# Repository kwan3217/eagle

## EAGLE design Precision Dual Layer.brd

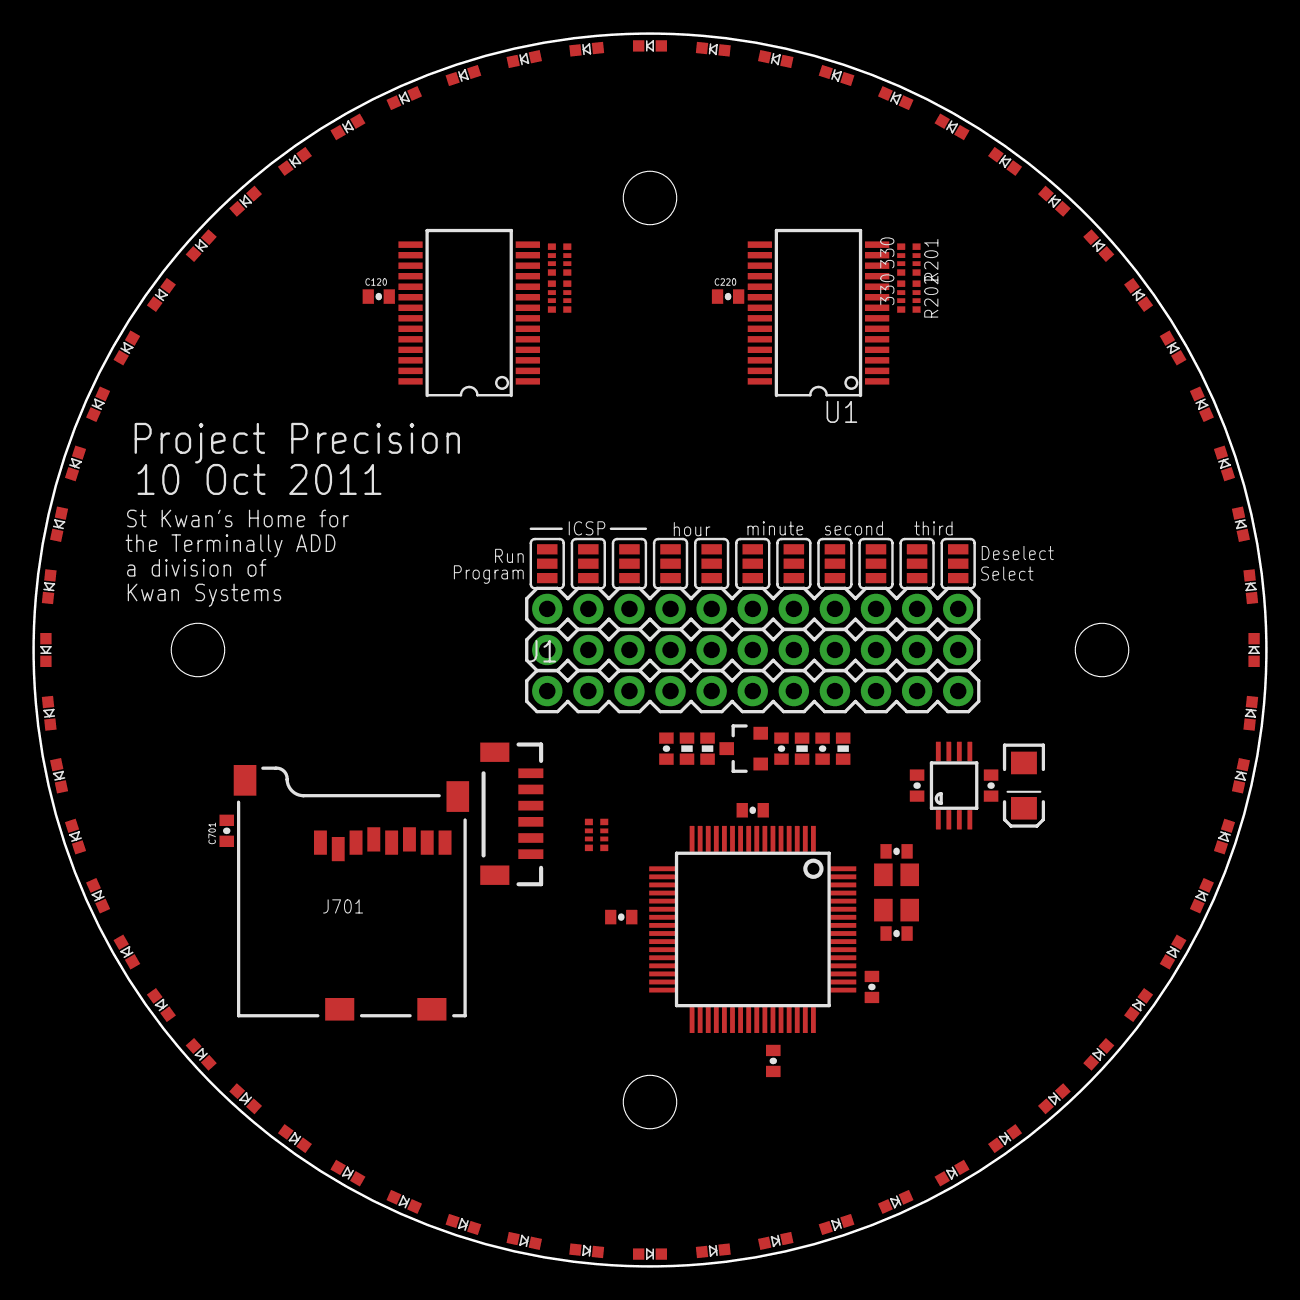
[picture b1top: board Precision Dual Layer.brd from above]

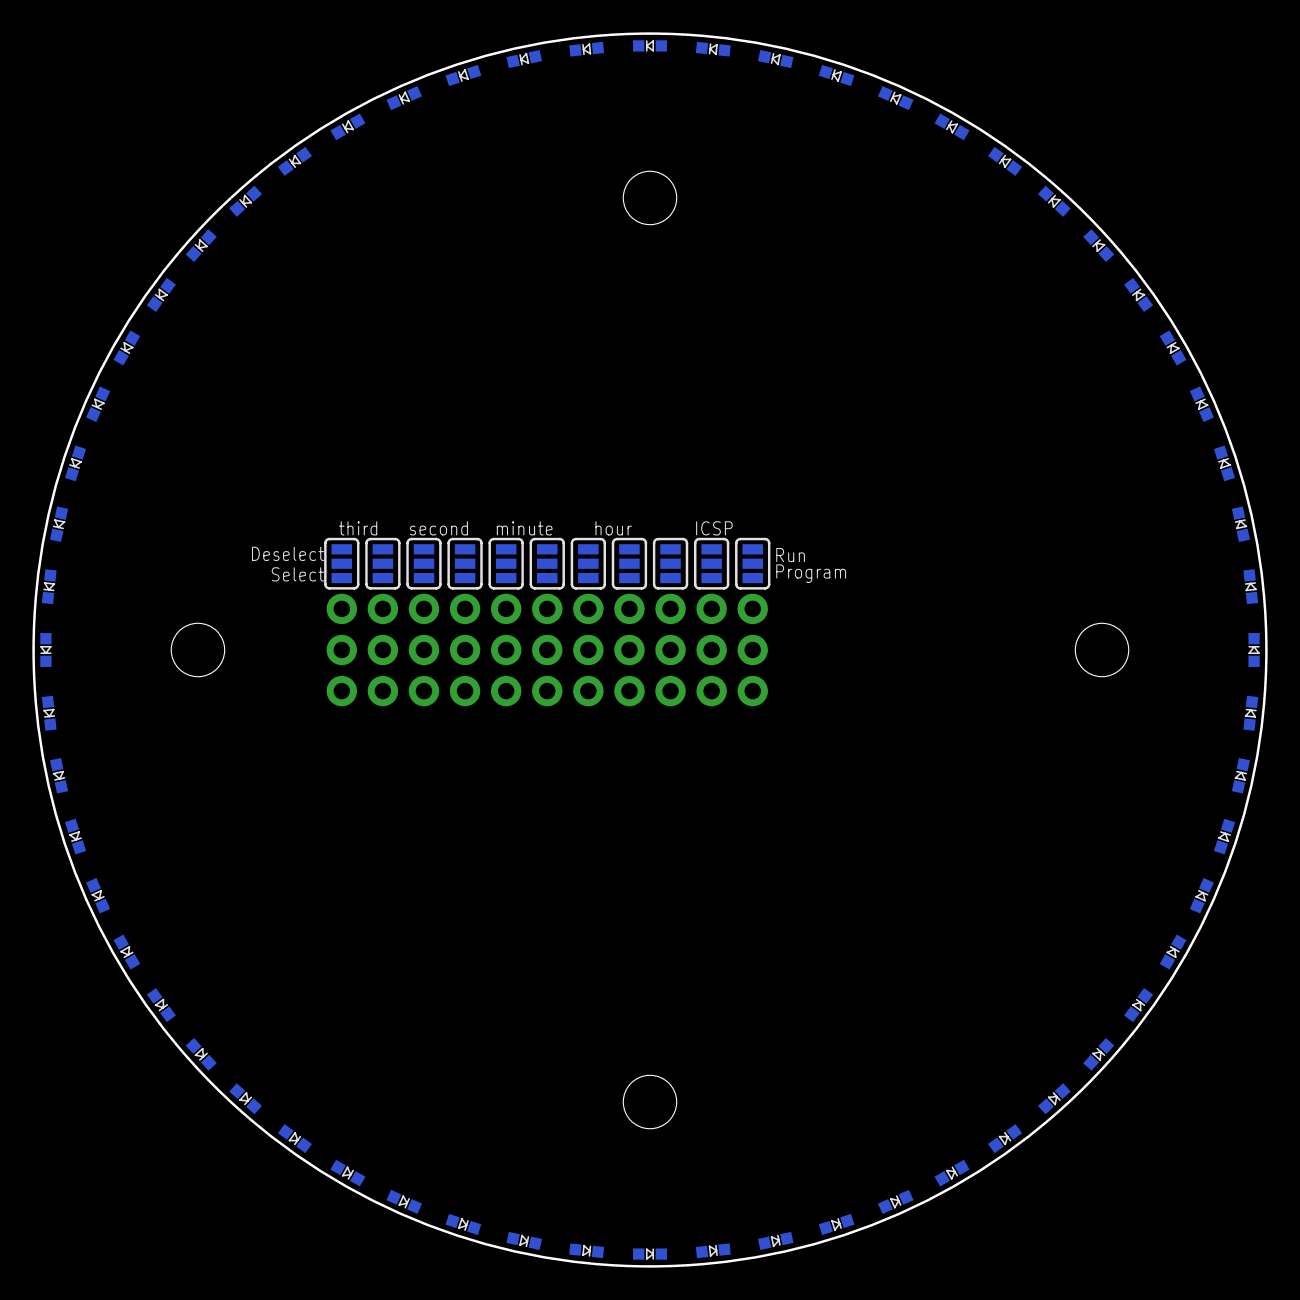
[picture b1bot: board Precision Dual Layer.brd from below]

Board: 2 copper layers, 76.2 x 76.2 mm, 181 parts (71 on the bottom side), 89 nets, no tracks yet.

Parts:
C010, C201: 1uF; 0402-CAP
C020, C030, C461, C462: 18pF; 0402-CAP
C120, C220, C407, C423, C443, C451, C701: 100nF; 0402-CAP
C202: 2.2uF tant; EIA3216
C203: 470pF; 0402-CAP
D00, D01, D02, D03, D04, D05, D06, D07, D08, D09, D10, D11, D12, D13, D14, D15, D16, D17, D18, D19, D20, D21, D22, D23, D24, D25, D26, D27, D28, D29, D30, D31, D32, D33, D34, D35, D36, D37, D38, D39, D40, D41, D42, D43, D44, D45, D46, D47, D48, D49, D50, D51, D52, D53, D54, D55, D56, D57, D58, D59, D60, D61, D62, D63, D64, D65, D66, D67, D68, D69, D70, D71, D72, D73, D74, D75, D76, D77, D78, D79, D80, D81, D82, D83, D84, D85, D86, D87, D88, D89, D90, D91, D92, D93, D94, D95, D96, D97, D98, D99, D100, D101, D102, D103, D104, D105, D106, D107, D108, D109, D110, D111, D112, D113, D114, D115, D116, D117, D118, D119: LED0603_SIDE
J1, J101, J401: 1X11
J403: EM406; EM406@1
J701: USD-SOCKETNEW; MICRO-SD-SOCKET-PP
JP3, JP4, JP5, JP6: STAND-OFF
Q002: PMOS; SOT23-3
R011: 100k; 0402-RES
R020, R030: 33; 0402-RES
R031: 1.5k; 0402-RES
R101, R102, R201, R202: 330; CRA04
R400: 10k; CRA04
SJ1, SJ2, SJ3, SJ4, SJ5, SJ6, SJ7, SJ8, SJ9, SJ10, SJ11, SJ12, SJ13, SJ14, SJ15, SJ16, SJ17, SJ18, SJ19, SJ20, SJ21, SJ22: SJ_3
U1, U101: PIC16F1933SS; SSOP28
U201: 5219; MSOP08
U401: LPC2148; SQFP-S-10X10-64
Y1: TSX-3225; CRYSTAL_SMD

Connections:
BSL: J1.4, J401.4, R400.7, U401.41
CLK_RESET: SJ2.2, SJ4.2, SJ6.2, SJ8.2, U101.7
CLK_RESET2: SJ12.2, SJ14.2, SJ16.2, SJ18.2, U1.7
CLK_TICK: SJ1.2, SJ3.2, SJ5.2, SJ7.2, U101.6
CLK_TICK2: SJ13.2, SJ15.2, SJ17.2, SJ21.2, U1.6
COL0: D00.C, D10.C, D20.C, D30.C, D40.C, D50.C, U101.15
COL1: D01.C, D11.C, D21.C, D31.C, D41.C, D51.C, U101.16
COL2: D02.C, D12.C, D22.C, D32.C, D42.C, D52.C, U101.17
COL3: D03.C, D13.C, D23.C, D33.C, D43.C, D53.C, U101.18
COL4: D04.C, D14.C, D24.C, D34.C, D44.C, D54.C, U101.21
COL5: D05.C, D15.C, D25.C, D35.C, D45.C, D55.C, U101.22
COL6: D06.C, D16.C, D26.C, D36.C, D46.C, D56.C, U101.23
COL7: D07.C, D17.C, D27.C, D37.C, D47.C, D57.C, U101.24
COL8: D08.C, D18.C, D28.C, D38.C, D48.C, D58.C, U101.25
COL9: D09.C, D19.C, D29.C, D39.C, D49.C, D59.C, U101.26
COL10: D60.C, D70.C, D80.C, D90.C, D100.C, D110.C, U1.15
COL11: D61.C, D71.C, D81.C, D91.C, D101.C, D111.C, U1.16
COL12: D62.C, D72.C, D82.C, D92.C, D102.C, D112.C, U1.17
COL13: D63.C, D73.C, D83.C, D93.C, D103.C, D113.C, U1.18
COL14: D64.C, D74.C, D84.C, D94.C, D104.C, D114.C, U1.21
COL15: D65.C, D75.C, D85.C, D95.C, D105.C, D115.C, U1.22
COL16: D66.C, D76.C, D86.C, D96.C, D106.C, D116.C, U1.23
COL17: D67.C, D77.C, D87.C, D97.C, D107.C, D117.C, U1.24
COL18: D68.C, D78.C, D88.C, D98.C, D108.C, D118.C, U1.25
COL19: D69.C, D79.C, D89.C, D99.C, D109.C, D119.C, U1.26
CS0: J701.2, U401.31
GND: C010.2, C020.2, C030.2, C120.1, C201.2, C202.C, C203.2, C220.1, C407.2, C423.2, C443.2, C451.2, C461.1, C462.1, C701.2, J1.9, J401.9, J403.1, J403.5, J701.6, J701.CD2, J701.GND1, R011.1, SJ1.1, SJ2.1, SJ3.1, SJ4.1, SJ5.1, SJ6.1, SJ7.1, SJ8.1, SJ10.1, SJ11.1, SJ12.1, SJ13.1, SJ14.1, SJ15.1, SJ16.1, SJ17.1, SJ18.1, SJ20.1, SJ21.1, SJ22.1, U1.8, U1.19, U101.8, U101.19, U201.5, U201.6, U201.7, U201.8, U401.6, U401.18, U401.25, U401.42, U401.50, U401.59, Y1.2, Y1.4
H_RST: J101.10, SJ2.3, SJ12.3, U401.38
H_TICK: J101.11, SJ1.3, SJ21.3, U401.39
ISPCLK: SJ11.2, U101.27
ISPCLK2: SJ22.2, U1.27
ISPCLKC: J101.2, SJ11.3, SJ22.3
ISPDAT: SJ10.2, U101.28
ISPDAT2: SJ20.2, U1.28
ISPDATC: J101.1, SJ10.3, SJ20.3
MCLR: SJ9.2, U101.1
MCLR2: SJ19.2, U1.1
MCLRC: J101.3, SJ9.3, SJ19.3
MISO0: J701.7, U401.29
MOSI0: J701.3, U401.30
M_RST: J101.8, SJ4.3, SJ14.3, U401.35
M_TICK: J101.9, SJ3.3, SJ13.3, U401.37
unnamed: C203.1, U201.4
PPS: J403.6, U401.46
QDRAIN: Q002.3, R031.1
RESET: J1.3, J401.3, R400.8, U401.57
ROW00: D00.A, D01.A, D02.A, D03.A, D04.A, D05.A, D06.A, D07.A, D08.A, D09.A, R101.8
ROW00C: R101.1, U101.14
ROW10: D10.A, D11.A, D12.A, D13.A, D14.A, D15.A, D16.A, D17.A, D18.A, D19.A, R101.7
ROW10C: R101.2, U101.13
ROW20: D20.A, D21.A, D22.A, D23.A, D24.A, D25.A, D26.A, D27.A, D28.A, D29.A, R101.6
ROW20C: R101.3, U101.12
ROW30: D30.A, D31.A, D32.A, D33.A, D34.A, D35.A, D36.A, D37.A, D38.A, D39.A, R102.7
ROW30C: R102.2, U101.9
ROW40: D40.A, D41.A, D42.A, D43.A, D44.A, D45.A, D46.A, D47.A, D48.A, D49.A, R102.8
ROW40C: R102.1, U101.10
ROW50: D50.A, D51.A, D52.A, D53.A, D54.A, D55.A, D56.A, D57.A, D58.A, D59.A, R101.5
ROW50C: R101.4, U101.11
ROW200: D60.A, D61.A, D62.A, D63.A, D64.A, D65.A, D66.A, D67.A, D68.A, D69.A, R201.8
ROW200C: R201.1, U1.14
ROW210: D70.A, D71.A, D72.A, D73.A, D74.A, D75.A, D76.A, D77.A, D78.A, D79.A, R201.7
ROW210C: R201.2, U1.13
ROW220: D80.A, D81.A, D82.A, D83.A, D84.A, D85.A, D86.A, D87.A, D88.A, D89.A, R201.6
ROW220C: R201.3, U1.12
ROW230: D90.A, D91.A, D92.A, D93.A, D94.A, D95.A, D96.A, D97.A, D98.A, D99.A, R202.7
ROW230C: R202.2, U1.9
ROW240: D100.A, D101.A, D102.A, D103.A, D104.A, D105.A, D106.A, D107.A, D108.A, D109.A, R202.8
ROW240C: R202.1, U1.10
ROW250: D110.A, D111.A, D112.A, D113.A, D114.A, D115.A, D116.A, D117.A, D118.A, D119.A, R201.5
ROW250C: R201.4, U1.11
RX0: J1.2, J401.2, J403.4, U401.21
RX1: J1.11, J401.11, U401.34
SCK0: J701.5, U401.27
S_RST: J101.6, SJ6.3, SJ16.3, U401.47
S_TICK: J101.7, SJ5.3, SJ15.3, U401.53
TX0: J1.1, J401.1, J403.3, U401.19
TX1: J1.10, J401.10, U401.33
T_RST: J101.4, SJ8.3, SJ18.3
T_TICK: J101.5, SJ7.3, SJ17.3
USBCONN_D+: J1.5, J401.5, R030.2, R031.2
USBCONN_D-: J1.7, J401.7, R020.2
USBD+: C030.1, R030.1, U401.10
USBD-: C020.1, R020.1, U401.11
USB_ON: R400.3, U401.58
USB_SOFTCONNECT: Q002.1, R400.5, U401.17
VBUS: C010.1, C120.2, C201.1, C220.2, J1.8, J401.8, J403.2, R011.2, R400.6, SJ9.1, SJ19.1, U1.20, U101.20, U201.1, U201.2
VCC: C202.A, C407.1, C423.1, C443.1, C451.1, C701.1, J1.6, J401.6, J701.4, Q002.2, R400.1, R400.2, R400.4, U201.3, U401.3, U401.7, U401.23, U401.43, U401.49, U401.51, U401.63
XTAL1: C462.2, U401.62, Y1.3
XTAL2: C461.2, U401.61, Y1.1

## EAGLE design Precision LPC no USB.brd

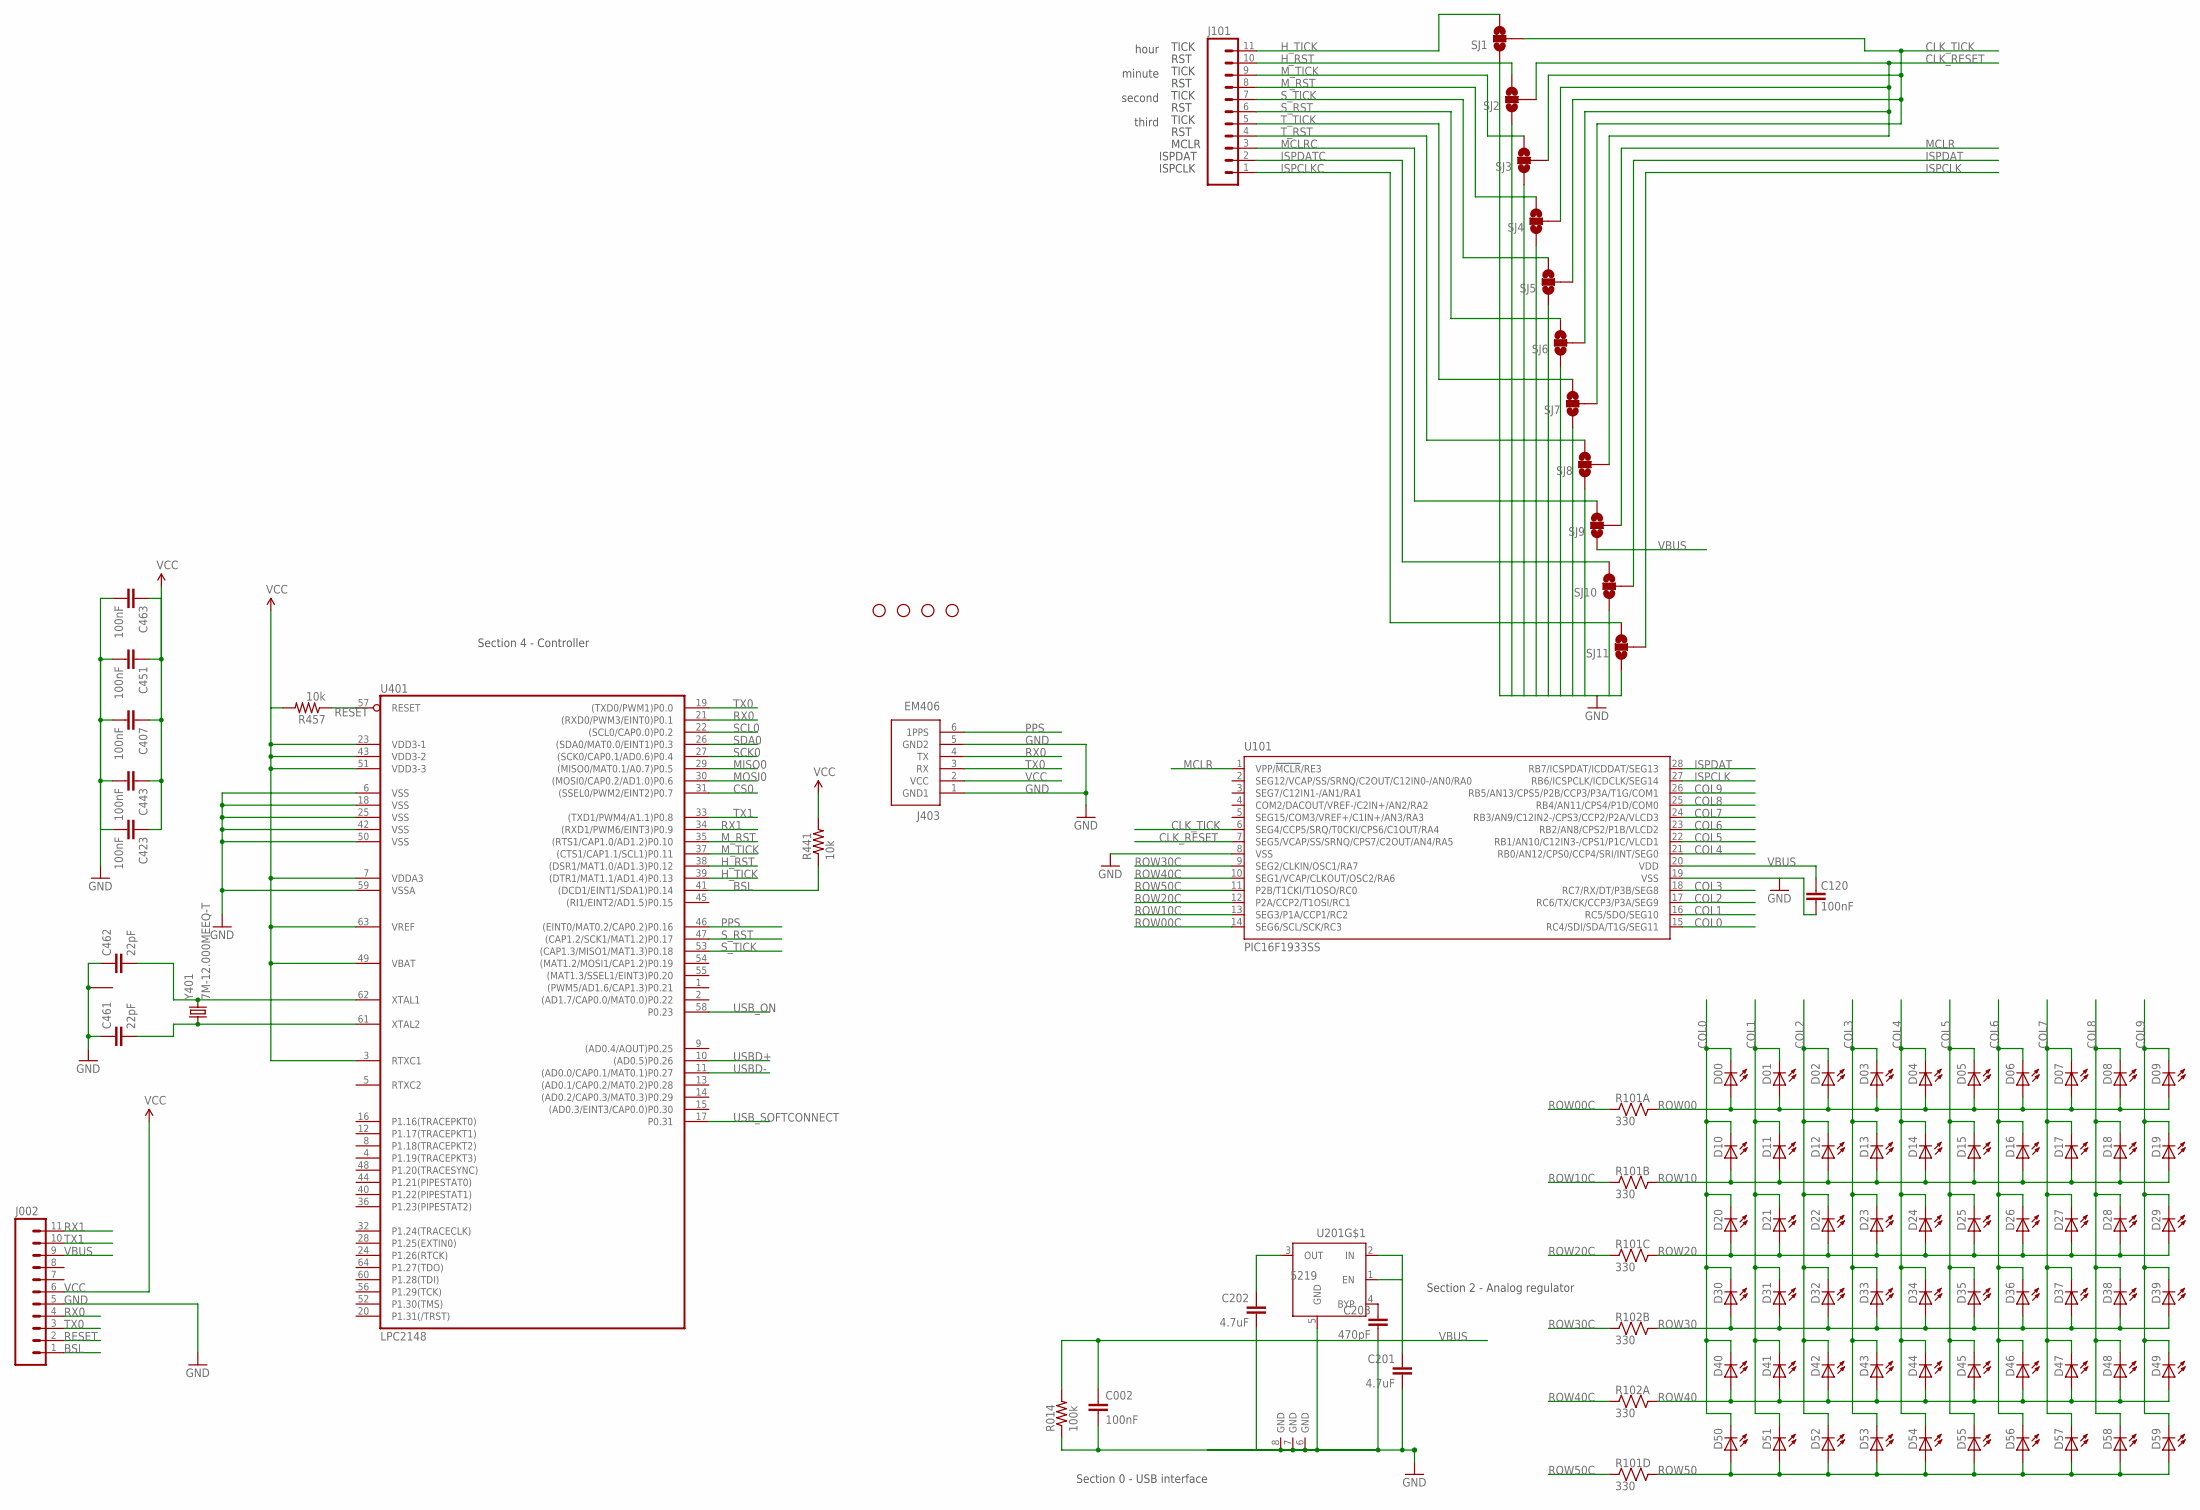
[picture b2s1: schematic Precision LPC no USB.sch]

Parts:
C002, C120, C407, C423, C443, C451, C463: 100nF; 0402-CAP
C201, C202: 4.7uF; 0402-CAP
C203: 470pF; 0402-CAP
C461, C462: 22pF; 0402-CAP
D00, D01, D02, D03, D04, D05, D06, D07, D08, D09, D10, D11, D12, D13, D14, D15, D16, D17, D18, D19, D20, D21, D22, D23, D24, D25, D26, D27, D28, D29, D30, D31, D32, D33, D34, D35, D36, D37, D38, D39, D40, D41, D42, D43, D44, D45, D46, D47, D48, D49, D50, D51, D52, D53, D54, D55, D56, D57, D58, D59: LED3MM
J002, J101: M11PTH; 1X11
J403: EM406; EM406@1
JP3, JP4, JP5, JP6: STAND-OFF
R014: 100k; 0402-RES
R101, R102: 330; CRA06
R441, R457: 10k; 0402-RES
SJ1, SJ2, SJ3, SJ4, SJ5, SJ6, SJ7, SJ8, SJ9, SJ10, SJ11: SOLDERJUMPER_2WAYS; SJ_3
U101: PIC16F1933SS; SSOP28
U201: 5219; MSOP08
U401: LPC2148; SQFP-S-10X10-64
Y401: 7M-12.000MEEQ-T; CRYSTAL_SMD

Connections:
BSL: J002.1, R441.1, U401.41 ((DCD1/EINT1/SDA1)P0.14)
CLK_RESET: SJ2.2, SJ4.2, SJ6.2, SJ8.2, U101.7 (SEG5/VCAP/SS/SRNQ/CPS7/C2OUT/AN4/RA5)
CLK_TICK: SJ1.2, SJ3.2, SJ5.2, SJ7.2, U101.6 (SEG4/CCP5/SRQ/T0CKI/CPS6/C1OUT/RA4)
COL0: D00.K (C), D10.K (C), D20.K (C), D30.K (C), D40.K (C), D50.K (C), U101.15 (RC4/SDI/SDA/T1G/SEG11)
COL1: D01.K (C), D11.K (C), D21.K (C), D31.K (C), D41.K (C), D51.K (C), U101.16 (RC5/SDO/SEG10)
COL2: D02.K (C), D12.K (C), D22.K (C), D32.K (C), D42.K (C), D52.K (C), U101.17 (RC6/TX/CK/CCP3/P3A/SEG9)
COL3: D03.K (C), D13.K (C), D23.K (C), D33.K (C), D43.K (C), D53.K (C), U101.18 (RC7/RX/DT/P3B/SEG8)
COL4: D04.K (C), D14.K (C), D24.K (C), D34.K (C), D44.K (C), D54.K (C), U101.21 (RB0/AN12/CPS0/CCP4/SRI/INT/SEG0)
COL5: D05.K (C), D15.K (C), D25.K (C), D35.K (C), D45.K (C), D55.K (C), U101.22 (RB1/AN10/C12IN3-/CPS1/P1C/VLCD1)
COL6: D06.K (C), D16.K (C), D26.K (C), D36.K (C), D46.K (C), D56.K (C), U101.23 (RB2/AN8/CPS2/P1B/VLCD2)
COL7: D07.K (C), D17.K (C), D27.K (C), D37.K (C), D47.K (C), D57.K (C), U101.24 (RB3/AN9/C12IN2-/CPS3/CCP2/P2A/VLCD3)
COL8: D08.K (C), D18.K (C), D28.K (C), D38.K (C), D48.K (C), D58.K (C), U101.25 (RB4/AN11/CPS4/P1D/COM0)
COL9: D09.K (C), D19.K (C), D29.K (C), D39.K (C), D49.K (C), D59.K (C), U101.26 (RB5/AN13/CPS5/P2B/CCP3/P3A/T1G/COM1)
CS0: U401.31 ((SSEL0/PWM2/EINT2)P0.7)
GND: C002.2, C120.1, C201.2, C202.2, C203.2, C407.2, C423.2, C443.2, C451.2, C461.1, C462.1, C463.2, J002.5, J403.1 (GND1), J403.5 (GND2), R014.1, SJ1.1, SJ2.1, SJ3.1, SJ4.1, SJ5.1, SJ6.1, SJ7.1, SJ8.1, SJ10.1, SJ11.1, U101.8 (VSS), U101.19 (VSS), U201.5 (GND), U201.6 (GND), U201.7 (GND), U201.8 (GND), U401.6 (VSS), U401.18 (VSS), U401.25 (VSS), U401.42 (VSS), U401.50 (VSS), U401.59 (VSSA), Y401.2 (1), Y401.4 (1)
H_RST: J101.10, SJ2.3, U401.38 ((DSR1/MAT1.0/AD1.3)P0.12)
H_TICK: J101.11, SJ1.3, U401.39 ((DTR1/MAT1.1/AD1.4)P0.13)
ISPCLK: SJ11.2, U101.27 (RB6/ICSPCLK/ICDCLK/SEG14)
ISPCLKC: J101.1, SJ11.3
ISPDAT: SJ10.2, U101.28 (RB7/ICSPDAT/ICDDAT/SEG13)
ISPDATC: J101.2, SJ10.3
MCLR: SJ9.2, U101.1 (VPP/!MCLR!/RE3)
MCLRC: J101.3, SJ9.3
MISO0: U401.29 ((MISO0/MAT0.1/A0.7)P0.5)
MOSI0: U401.30 ((MOSI0/CAP0.2/AD1.0)P0.6)
M_RST: J101.8, SJ4.3, U401.35 ((RTS1/CAP1.0/AD1.2)P0.10)
M_TICK: J101.9, SJ3.3, U401.37 ((CTS1/CAP1.1/SCL1)P0.11)
unnamed: C202.1, U201.3 (OUT)
unnamed: C203.1, U201.4 (BYP)
PPS: J403.6 (1PPS), U401.46 ((EINT0/MAT0.2/CAP0.2)P0.16)
RESET: J002.2, R457.1, U401.57 (RESET)
ROW00: D00.A, D01.A, D02.A, D03.A, D04.A, D05.A, D06.A, D07.A, D08.A, D09.A, R101.8 (2)
ROW00C: R101.1, U101.14 (SEG6/SCL/SCK/RC3)
ROW10: D10.A, D11.A, D12.A, D13.A, D14.A, D15.A, D16.A, D17.A, D18.A, D19.A, R101.7 (2)
ROW10C: R101.2 (1), U101.13 (SEG3/P1A/CCP1/RC2)
ROW20: D20.A, D21.A, D22.A, D23.A, D24.A, D25.A, D26.A, D27.A, D28.A, D29.A, R101.6 (2)
ROW20C: R101.3 (1), U101.12 (P2A/CCP2/T1OSI/RC1)
ROW30: D30.A, D31.A, D32.A, D33.A, D34.A, D35.A, D36.A, D37.A, D38.A, D39.A, R102.7 (2)
ROW30C: R102.2 (1), U101.9 (SEG2/CLKIN/OSC1/RA7)
ROW40: D40.A, D41.A, D42.A, D43.A, D44.A, D45.A, D46.A, D47.A, D48.A, D49.A, R102.8 (2)
ROW40C: R102.1, U101.10 (SEG1/VCAP/CLKOUT/OSC2/RA6)
ROW50: D50.A, D51.A, D52.A, D53.A, D54.A, D55.A, D56.A, D57.A, D58.A, D59.A, R101.5 (2)
ROW50C: R101.4 (1), U101.11 (P2B/T1CKI/T1OSO/RC0)
RX0: J002.4, J403.4 (TX), U401.21 ((RXD0/PWM3/EINT0)P0.1)
RX1: J002.11, U401.34 ((RXD1/PWM6/EINT3)P0.9)
SCK0: U401.27 ((SCK0/CAP0.1/AD0.6)P0.4)
SCL0: U401.22 ((SCL0/CAP0.0)P0.2)
SDA0: U401.26 ((SDA0/MAT0.0/EINT1)P0.3)
S_RST: J101.6, SJ6.3, U401.47 ((CAP1.2/SCK1/MAT1.2)P0.17)
S_TICK: J101.7, SJ5.3, U401.53 ((CAP1.3/MISO1/MAT1.3)P0.18)
TX0: J002.3, J403.3 (RX), U401.19 ((TXD0/PWM1)P0.0)
TX1: J002.10, U401.33 ((TXD1/PWM4/A1.1)P0.8)
T_RST: J101.4, SJ8.3
T_TICK: J101.5, SJ7.3
USBD+: U401.10 ((AD0.5)P0.26)
USBD-: U401.11 ((AD0.0/CAP0.1/MAT0.1)P0.27)
USB_ON: U401.58 (P0.23)
USB_SOFTCONNECT: U401.17 (P0.31)
VBUS: C002.1, C120.2, C201.1, J002.9, R014.2, SJ9.1, U101.20 (VDD), U201.1 (EN), U201.2 (IN)
VCC: C407.1, C423.1, C443.1, C451.1, C463.1, J002.6, J403.2 (VCC), R441.2, R457.2, U401.3 (RTXC1), U401.7 (VDDA3), U401.23 (VDD3-1), U401.43 (VDD3-2), U401.49 (VBAT), U401.51 (VDD3-3), U401.63 (VREF)
XTAL3: C462.2, U401.62 (XTAL1), Y401.3 (2)
XTAL4: C461.2, U401.61 (XTAL2), Y401.1

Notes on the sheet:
TICK
RST
hour
minute
second
third
MCLR
ISPCLK
ISPDAT
Section 0 - USB interface
Section 2 - Analog regulator
Section 4 - Controller

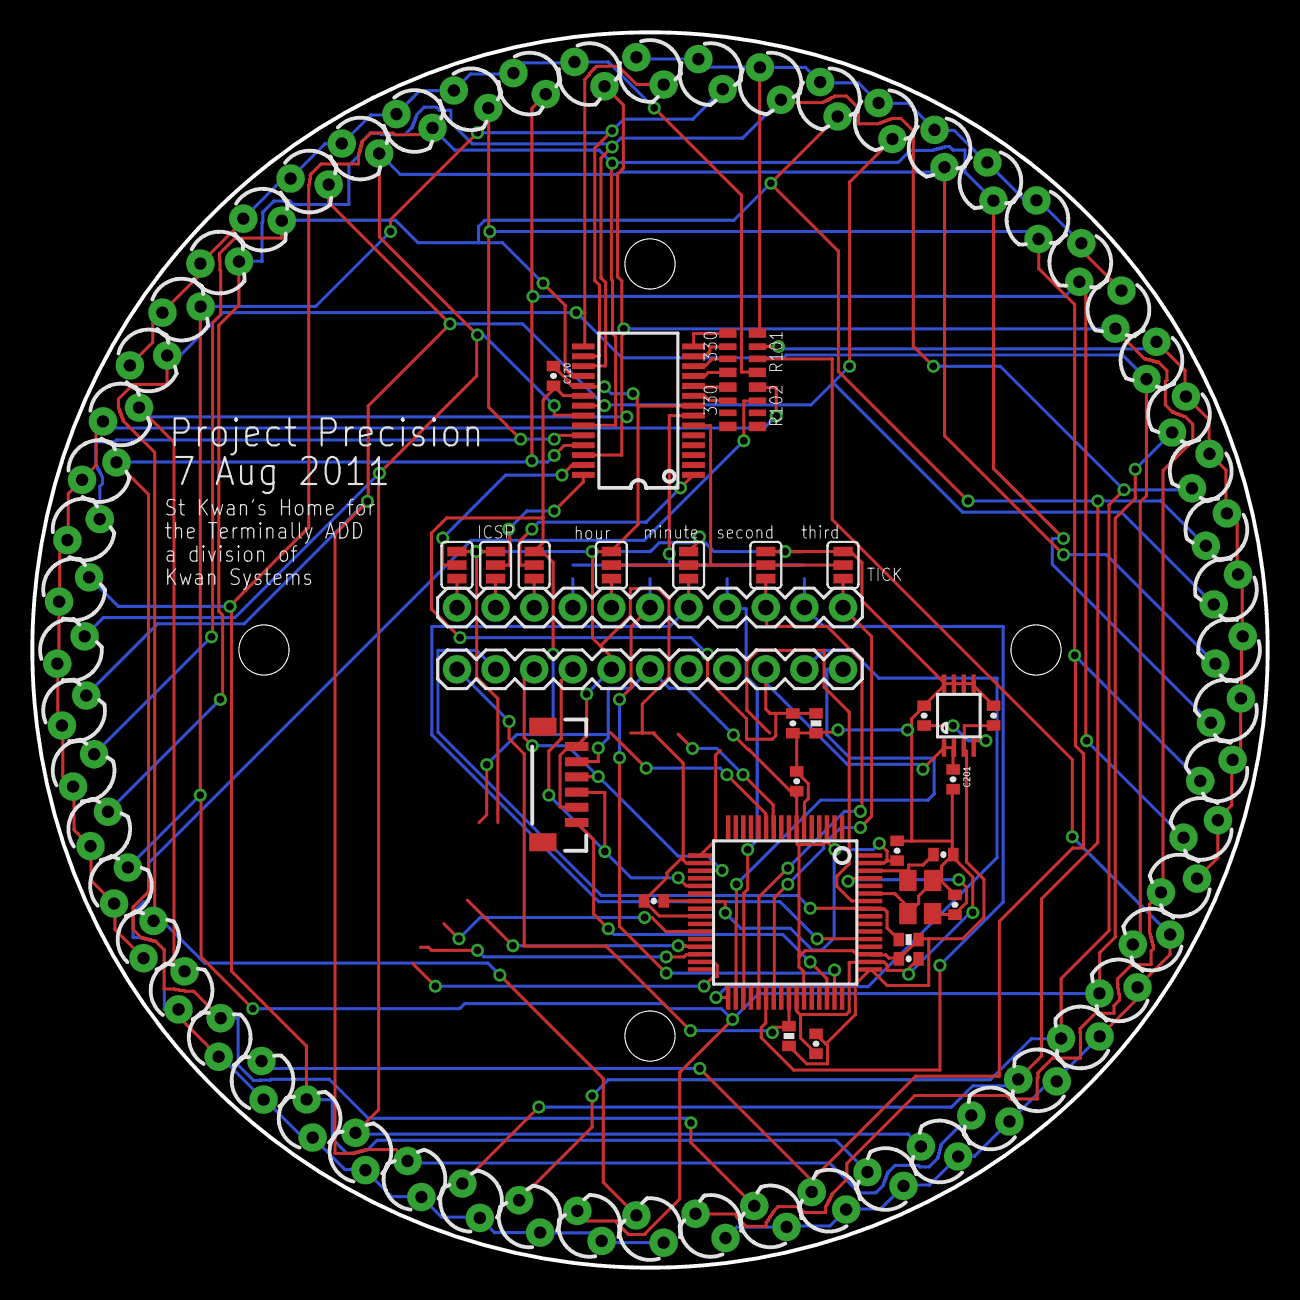
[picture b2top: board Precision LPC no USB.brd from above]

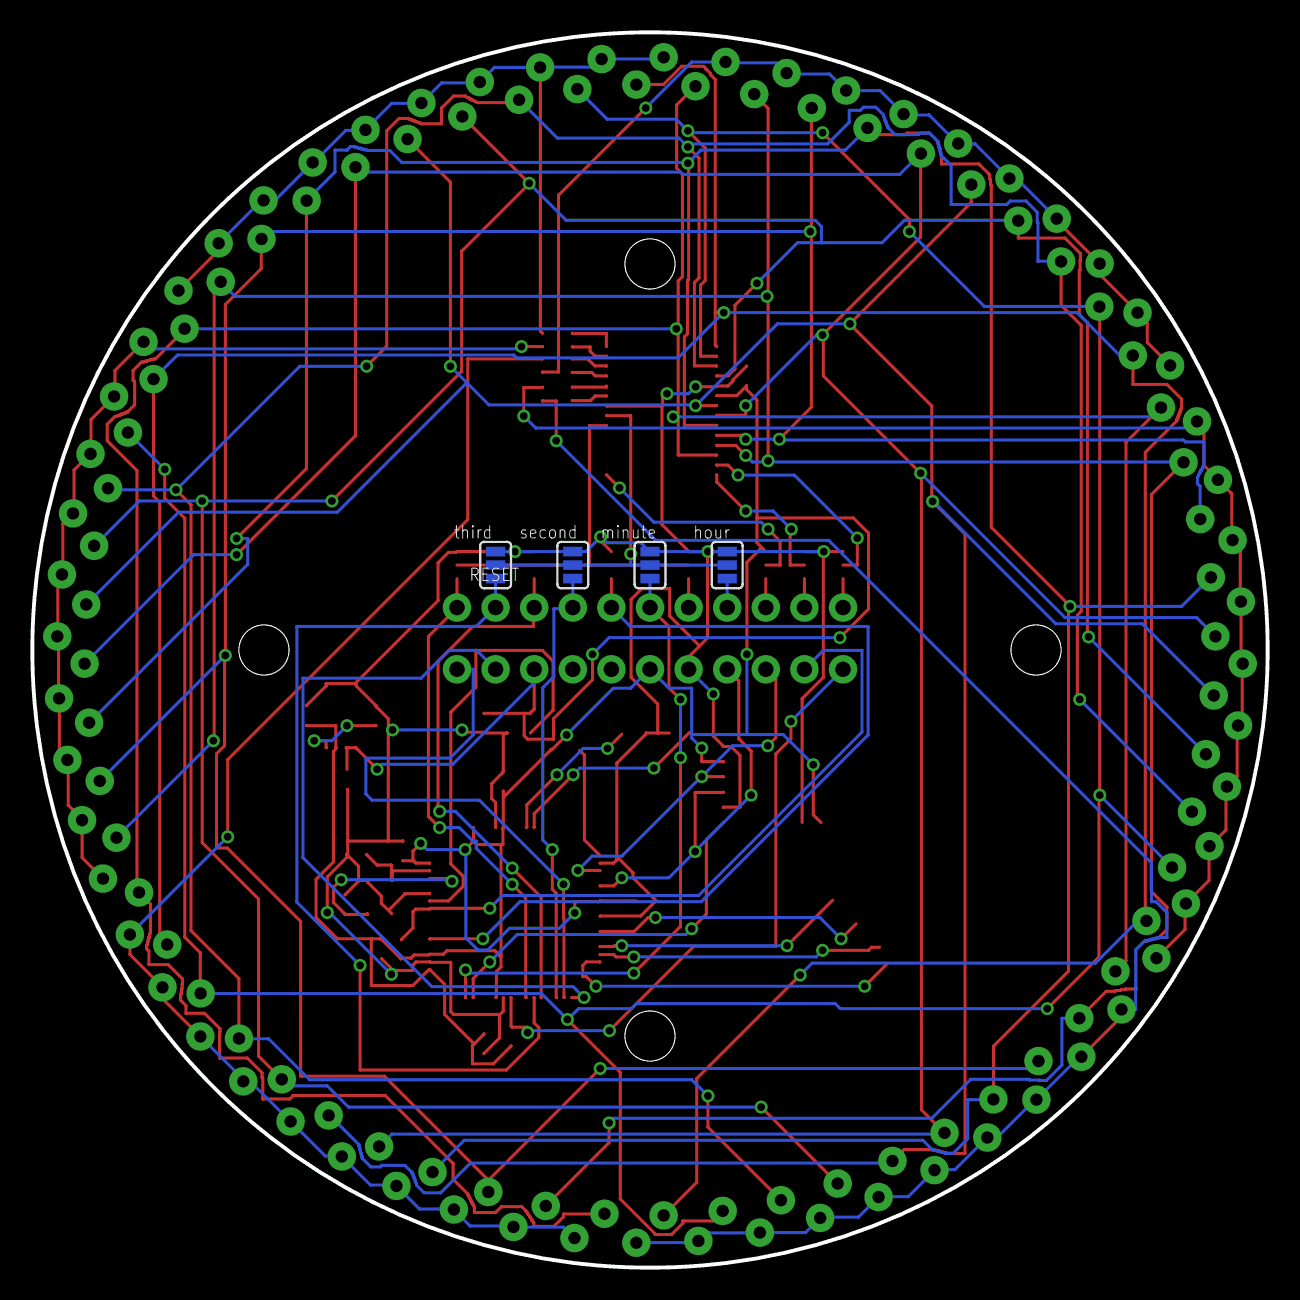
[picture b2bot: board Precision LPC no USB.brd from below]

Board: 2 copper layers, 81.3 x 81.3 mm, 99 parts (4 on the bottom side), 52 nets.

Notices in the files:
parts and their libraries:
SparkFun-Connectors: Licensing: CC v3.0 Share-Alike You are welcome to use this library for commercial purposes.
